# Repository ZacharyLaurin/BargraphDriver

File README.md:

# Bargraph Driver

For IN-13 / IN-9 Neon Tubes

## Description

This is a small 21x24mm driver module PCB designed for a single IN-13 or IN-9 neon bargraph tube. It fits on a breadboard and multiple modules can be chained together with U-shaped headers. Each module has an 8-bit DAC with a fixed address, controlled via I2C. The potentiometer is used to adjust the maximum glow length. Here is four tubes acting as a (not very accurate) spectrum analyzer: https://www.youtube.com/shorts/-yOVEOMO8Xs

In the resources folder you will find the datasheet for the IN-13 as well as the font I used on the silkscreen. I have also included the BOM. I personally got all of the components from Mouser and the boards printed at OSHPark. To power the tubes I am using a [NCH6300HV](https://omnixie.com/products/nch6300hv-nixie-hv-power-module) and to control them an Arduino UNO with this [MCP47X6 library](https://github.com/uChip/MCP47X6).

### Notes

* The SDA pad is right next to the +150V one so watch out as to not accidentally short them while soldering.
* Although the MCP4706's datasheet says that there are eight available addresses, it seems that most electronic suppliers only stock the first four. In my case I had to use two I2C buses to drive as many tubes as I wanted to (and had to do two chains of four tubes).
* You need some sort of frame to hold the tubes in place. I recommend the use of large zip ties near the base to keep them straight.

## Author

Zachary Laurin

## Version History

* 1.0.0
    * Initial Release

## License

This project is licensed under the GNU GPLv3 License - see the LICENSE.md file for details

## Acknowledgments

Thanks a lot to the users of the Arduino, KiCad EDA and Nixie Tubes Discord servers as well as to the people of neonixie-l and the EEVblog forum for their help.

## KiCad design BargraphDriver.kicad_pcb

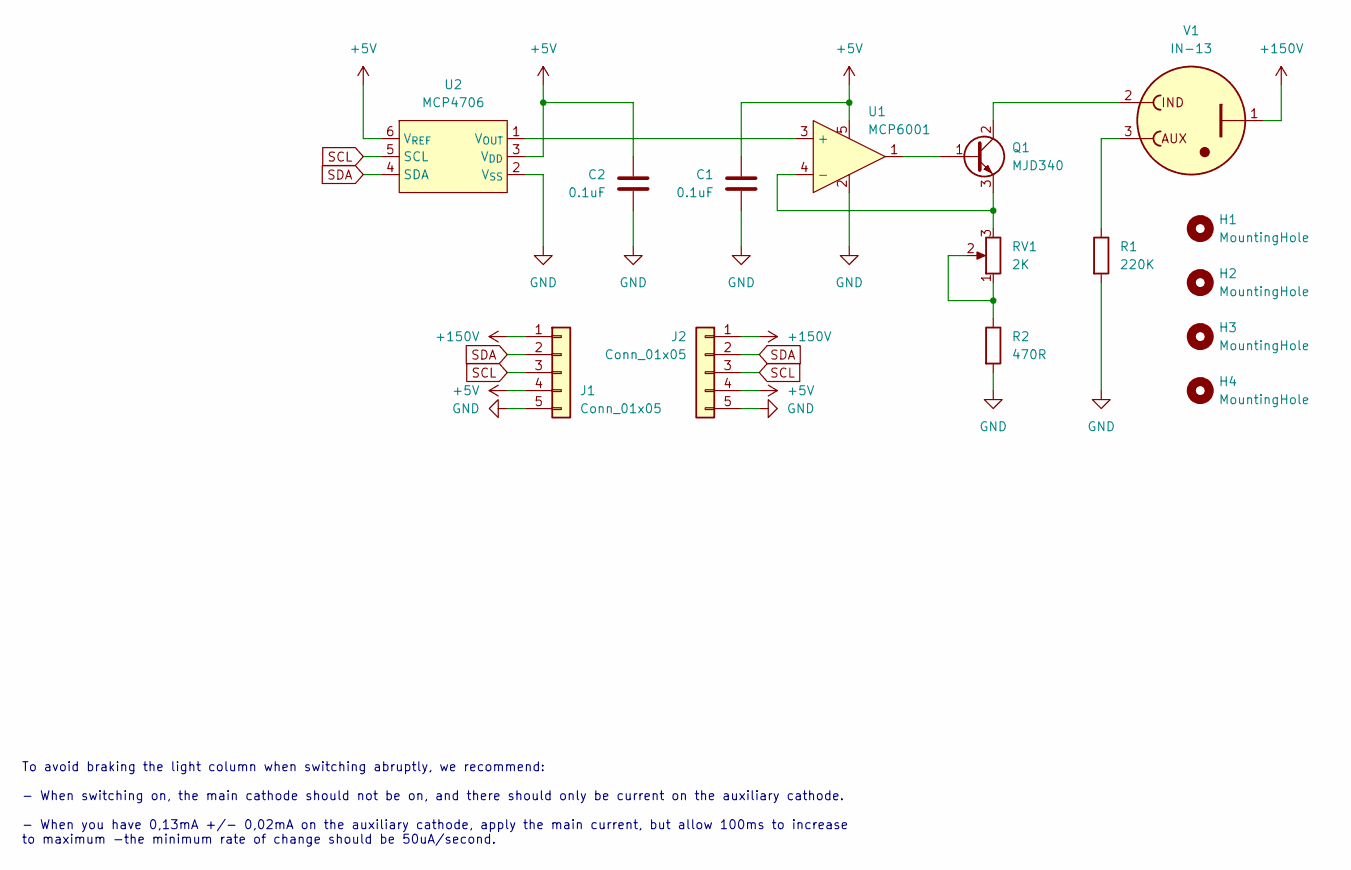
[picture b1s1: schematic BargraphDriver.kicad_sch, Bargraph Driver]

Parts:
C1, C2: 0.1uF; C_0603_1608Metric
H1, H2, H3, H4: MountingHole; MountingHoleM2
J1, J2: Conn_01x05; Connector
Q1: MJD340; TO-252-2
R1: 220K; R_1206_3216Metric
R2: 470R; R_1206_3216Metric
RV1: 2K; ST-4EB
U1: MCP6001; SOT-23-5
U2: MCP4706; SOT-23-6
V1: IN-13

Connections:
+5V: C1.1, C2.1, J1.4, J2.4, U1.5 (V_{DD}), U2.3 (V_{DD}), U2.6 (V_{REF})
+150V: J1.1, J2.1, V1.1 (A)
GND: C1.2, C2.2, J1.5, J2.5, R1.2, R2.2, U1.2 (GND), U2.2 (V_{SS})
unnamed: Q1.1 (B), U1.1 (OUT)
unnamed: Q1.2 (C), V1.2 (IND_Cathode)
unnamed: Q1.3 (E), RV1.3, U1.4 (-)
unnamed: R2.1, RV1.1, RV1.2
unnamed: U1.3 (+), U2.1 (V_{OUT})
unnamed: R1.1, V1.3 (AUX_Cathode)
SCL: J1.3, J2.3, U2.5 (SCL)
SDA: J1.2, J2.2, U2.4 (SDA)

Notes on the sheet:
To avoid braking the light column when switching abruptly, we recommend: - When switching on, the main cathode should not be on, and there should only be current on the auxiliary cathode. - When you have 0,13mA +/- 0,02mA on the auxiliary cathode, apply the main current, but allow 100ms to increase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

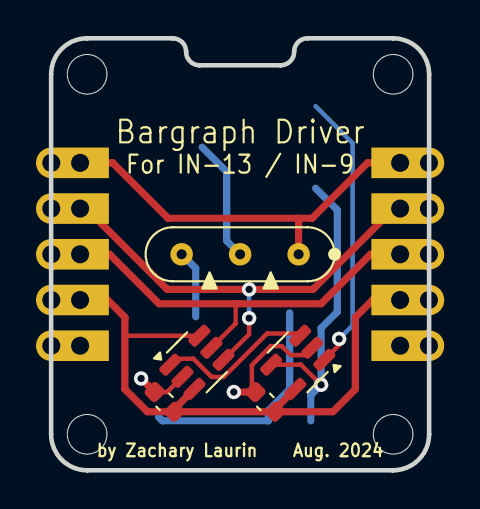
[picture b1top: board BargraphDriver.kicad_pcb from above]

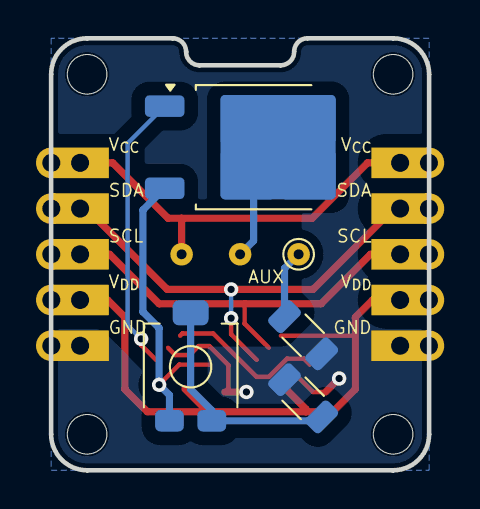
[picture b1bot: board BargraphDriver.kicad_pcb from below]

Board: 2 copper layers, 21.0 x 24.0 mm, 15 parts (5 on the bottom side), 11 nets.

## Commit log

2024-11-22 Description
2024-11-22 Grammar
2024-11-29 Exported schematic as PDF
2025-01-01 Fixed typos
